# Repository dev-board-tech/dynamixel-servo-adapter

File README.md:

# Dynamixel-Servo-Setup
 A simple utility to setup and test Dynamixel servo motors

 To build the application you need Qt community build and can be build on any platform supported by Qt, there are no special dependencies or external lib's used.

 Curently supports only DYNAMIXEL Protocol 1.0.

 Board thickness is mandatory to be 0.8mm because if is thicker or thinner the USB C cable will not enter or will be too lose.

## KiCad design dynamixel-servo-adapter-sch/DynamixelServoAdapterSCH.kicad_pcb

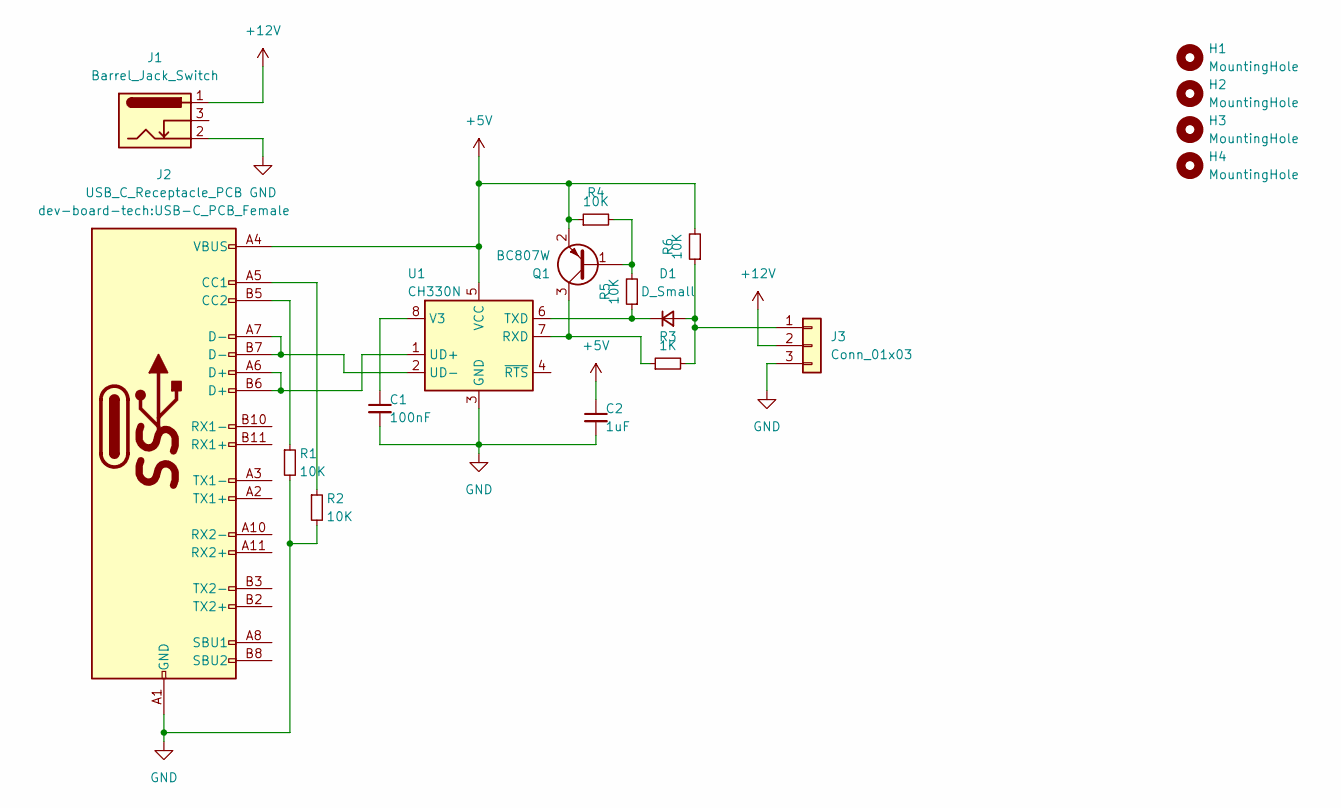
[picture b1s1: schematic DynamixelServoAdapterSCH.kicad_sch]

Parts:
C1: 100nF; C_0603_1608Metric
C2: 1uF; C_0805_2012Metric
D1: D_Small; D_0603_1608Metric
H1, H2, H3, H4: MountingHole; MountingHole_2.5mm
J1: Barrel_Jack_Switch; BarrelJack_GCT_DCJ200-10-A_Horizontal
J2: USB_C_Receptacle_PCB; USB-C_PCB_Female
J3: Conn_01x03; Molex_SPOX_5267-03A_1x03_P2.50mm_Vertical
Q1: BC807W; SOT-23
R1, R2, R4, R5, R6: 10K; R_0603_1608Metric
R3: 1K; R_0603_1608Metric
U1: CH330N; SOIC-8_3.9x4.9mm_P1.27mm

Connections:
+5V: C2.1, J2.A4 (VBUS), J2.A9 (VBUS), J2.B4 (VBUS), J2.B9 (VBUS), Q1.2 (E), R4.1, R6.2, U1.5 (VCC)
+12V: J1.1, J3.2
GND: C1.2, C2.2, J1.2, J2.A1 (GND), J2.A12 (GND), J2.B1 (GND), J2.B12 (GND), J3.3, R1.2, R2.2, U1.3 (GND)
unnamed: D1.2 (A), J3.1, R3.2, R6.1
unnamed: D1.1 (K), R5.1, U1.6 (TXD)
unnamed: J2.A5 (CC1), R2.1
unnamed: J2.B5 (CC2), R1.1
unnamed: Q1.1 (B), R4.2, R5.2
unnamed: Q1.3 (C), R3.1, U1.7 (RXD)
unnamed: J2.A6 (D+), J2.B6 (D+), U1.1 (UD+)
unnamed: J2.A7 (D-), J2.B7 (D-), U1.2 (UD-)
unnamed: C1.1, U1.8 (V3)

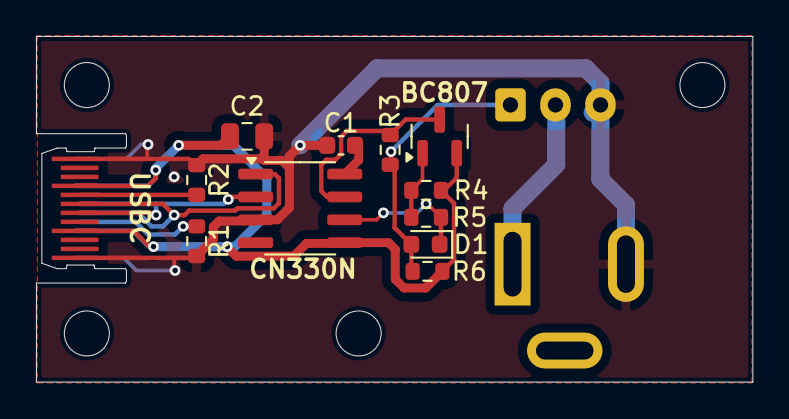
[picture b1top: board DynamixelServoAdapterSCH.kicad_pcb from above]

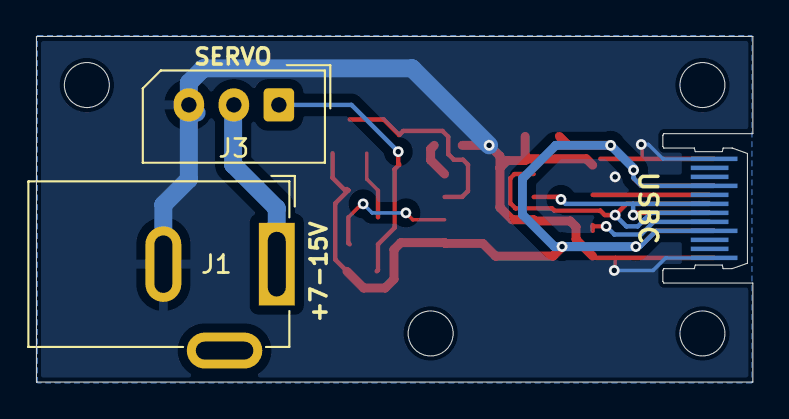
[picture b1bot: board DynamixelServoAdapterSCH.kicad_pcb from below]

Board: 2 copper layers, 39.8 x 19.2 mm, 18 parts (2 on the bottom side), 12 nets.

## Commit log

2024-08-02 First release
2024-08-02 Update repo
2025-11-25 Add servo and protocol documantation
